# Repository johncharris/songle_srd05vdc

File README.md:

# Optocoupler Relay Driver

This package implements an optocoupler-controlled relay driver circuit based on the schematic with PC817C optocoupler, S8050 transistor, and 5V relay components.

## Features

- **Electrical isolation**: Uses optocoupler for safe control from microcontrollers
- **5V relay control**: Optimized for standard 5V relay coils  
- **Flyback protection**: Built-in flyback diode to protect against voltage spikes
- **Standard interfaces**: Compatible with atopile ElectricLogic and ElectricPower interfaces

## Components

- **Relay**: 5V coil with NO/COM/NC contacts rated for high current switching
- **Control MOSFET**: N-channel MOSFET for relay coil switching  
- **Flyback diode**: Protection against inductive kickback from relay coil
- **Gate resistor**: Current limiting for MOSFET gate control

## Usage

```ato
import OptocouplerRelayDriver from "optocoupler-relay-driver/optocoupler-relay-driver.ato"

module MyProject:
    # Power supply
    power_5v = new ElectricPower
    assert power_5v.voltage within 5V +/- 5%
    
    # Control from microcontroller
    mcu_control_pin = new ElectricLogic
    
    # Load to be switched  
    load_hot = new Electrical
    load_neutral = new Electrical
    
    # Relay driver
    relay_driver = new OptocouplerRelayDriver
    
    # Connections
    power_5v ~ relay_driver.power_5v
    mcu_control_pin ~ relay_driver.control_input
    
    # Switch load through relay normally open contact
    load_hot ~ relay_driver.relay_com
    relay_driver.relay_no ~ load_neutral
```

## Interface

### Inputs
- `control_input: ElectricLogic` - Control signal from microcontroller (3.3V/5V logic)
- `power_5v: ElectricPower` - 5V power supply for relay coil (4.5V-5.5V)

### Outputs  
- `relay_no: Electrical` - Relay normally open contact
- `relay_com: Electrical` - Relay common contact
- `relay_nc: Electrical` - Relay normally closed contact

## Specifications

- **Control voltage**: 3.3V or 5V logic levels
- **Relay coil**: 5V ±10%, ~50mA
- **Contact rating**: 10A switching, 16A continuous at 250VAC
- **Isolation**: Optical isolation between control and power circuits

## Circuit Description

The circuit uses an optocoupler (PC817C equivalent) to provide electrical isolation between the control logic and the high-current relay circuit. When the control input is high, the optocoupler LED turns on, causing the phototransistor to conduct. This drives the base of the switching transistor (S8050 equivalent), which energizes the relay coil. A flyback diode protects against voltage spikes when the relay is de-energized.

## Contributing

Contributions to this package are welcome via pull requests on the GitHub repository.

## License

This atopile package is provided under the [MIT License](https://opensource.org/license/mit/).

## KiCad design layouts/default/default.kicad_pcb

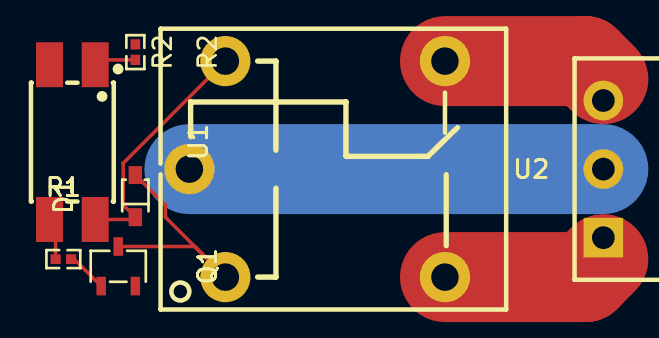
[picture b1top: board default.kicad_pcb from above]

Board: 2 copper layers, 7 parts (0 on the bottom side), 8 nets.

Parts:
D1: SOD-323_L1.8-W1.3-LS2.5-RD
Q1: SOT-23-3_L3.0-W1.7-P0.95-LS2.9-BR
R1, R2: 1kΩ ±1% 62.5mW; R0402
RLY1: RELAY-TH_SRD-XXVDC-XL-C
U1: OPTO-SMD-4_L4.6-W6.5-P2.54-LS10.3-TL
U2: CONN-TH_3P-P3.81_WJ15EDGRC-3.81-3P

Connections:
A: D1.2, Q1.3, RLY1.1
B: Q1.1, R1.2
VCC: D1.1, RLY1.4, U1.4
_1: R2.2, U1.1
_3: R1.1, U1.3
terminal_com: RLY1.5, U2.2
terminal_nc: RLY1.3, U2.3
terminal_no: RLY1.2, U2.1

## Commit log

2025-09-09 Updated the package info.
2025-09-12 Swapped out the connecter with a pluggable one.
